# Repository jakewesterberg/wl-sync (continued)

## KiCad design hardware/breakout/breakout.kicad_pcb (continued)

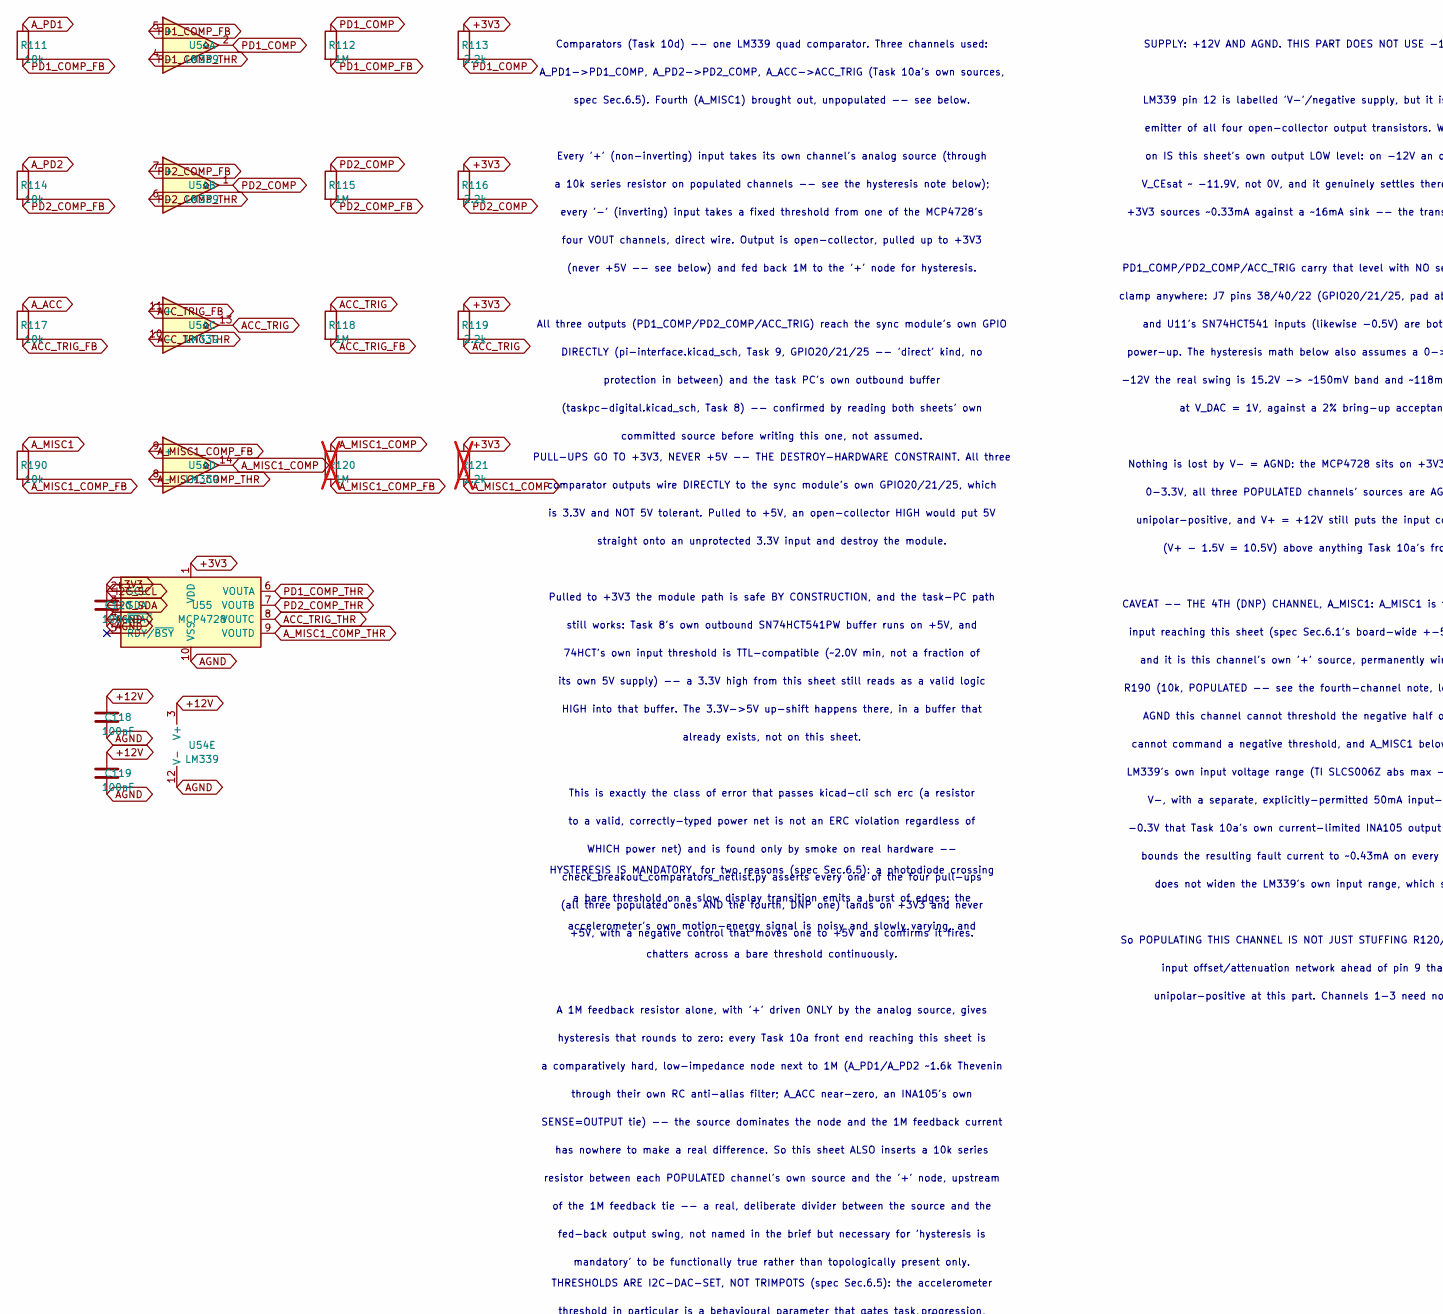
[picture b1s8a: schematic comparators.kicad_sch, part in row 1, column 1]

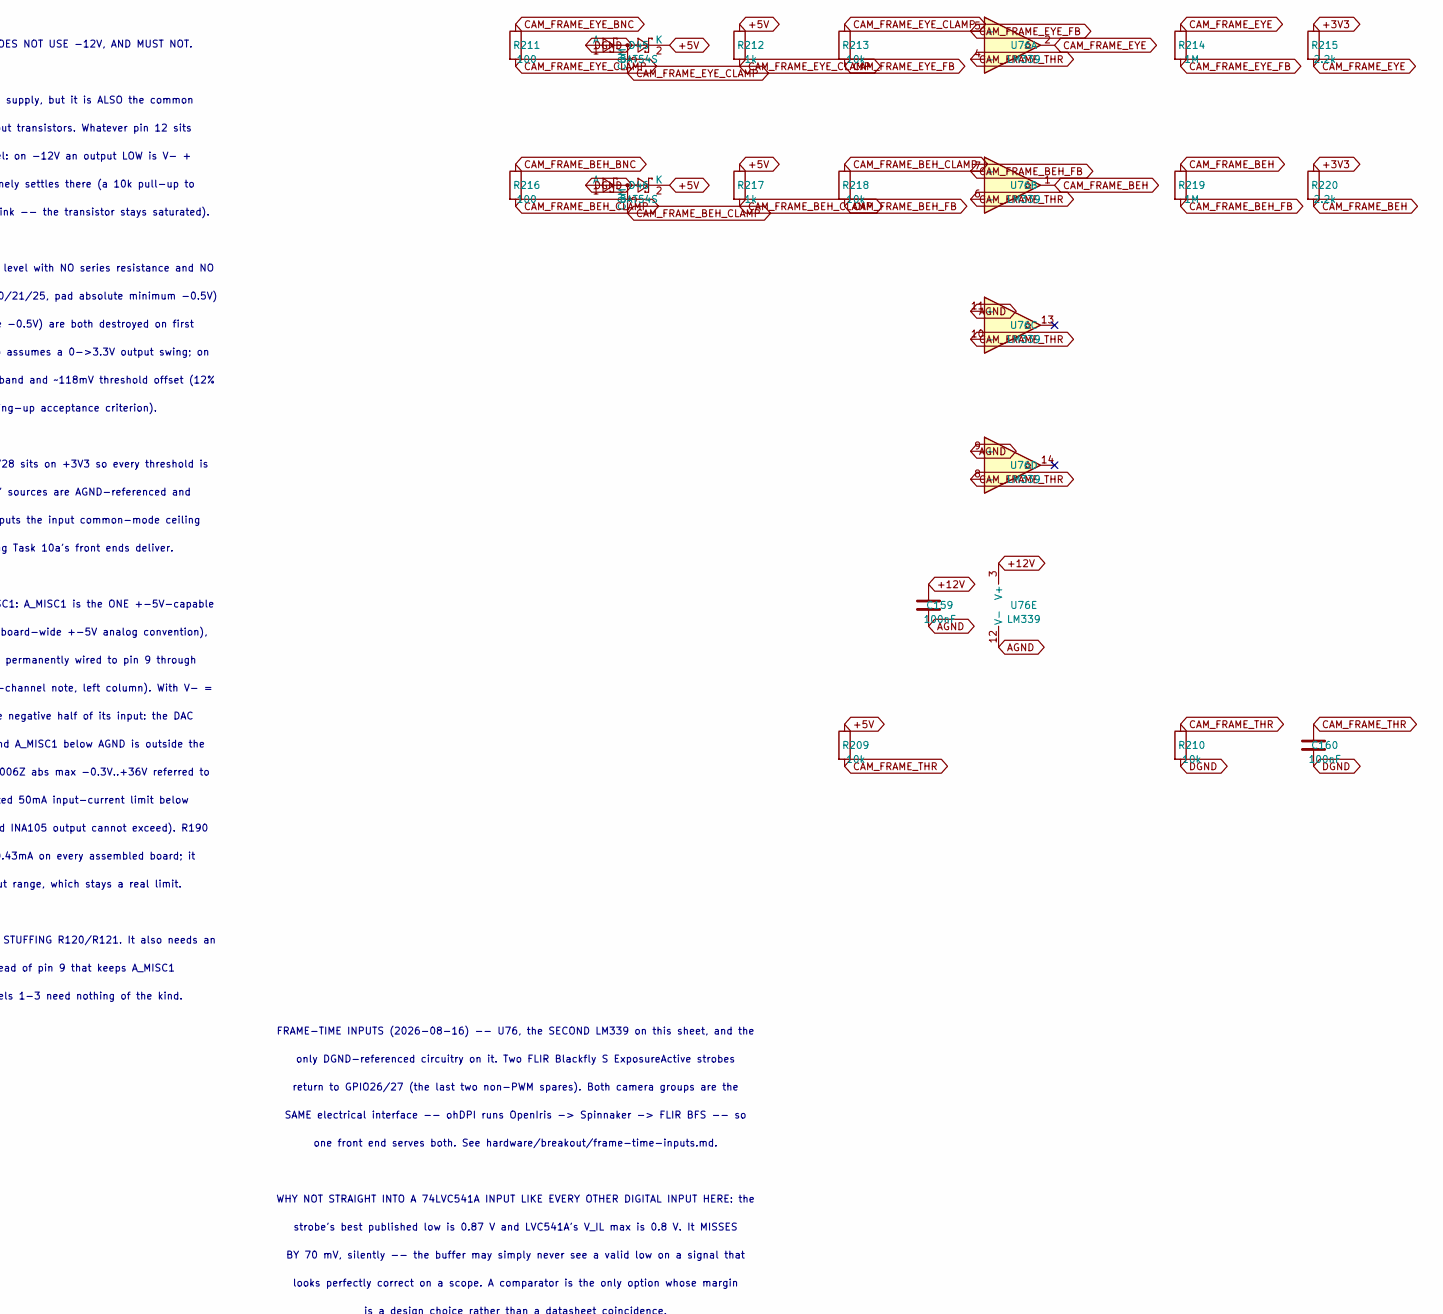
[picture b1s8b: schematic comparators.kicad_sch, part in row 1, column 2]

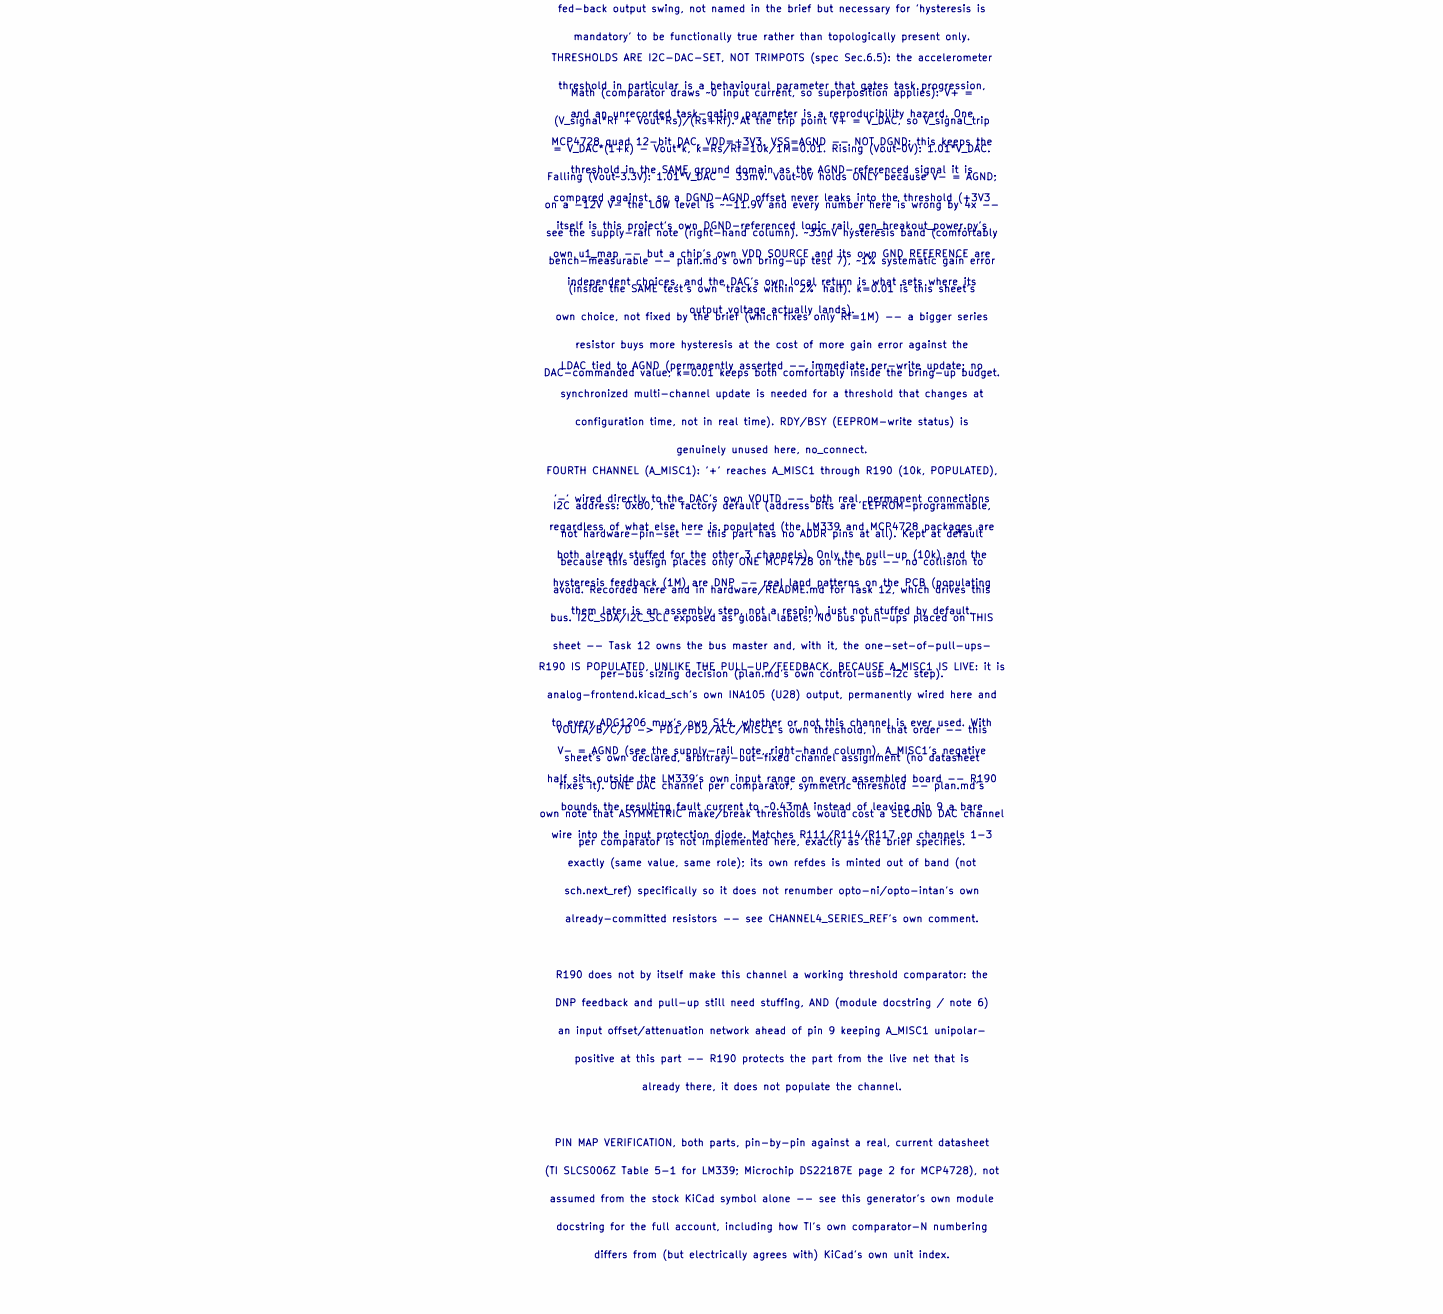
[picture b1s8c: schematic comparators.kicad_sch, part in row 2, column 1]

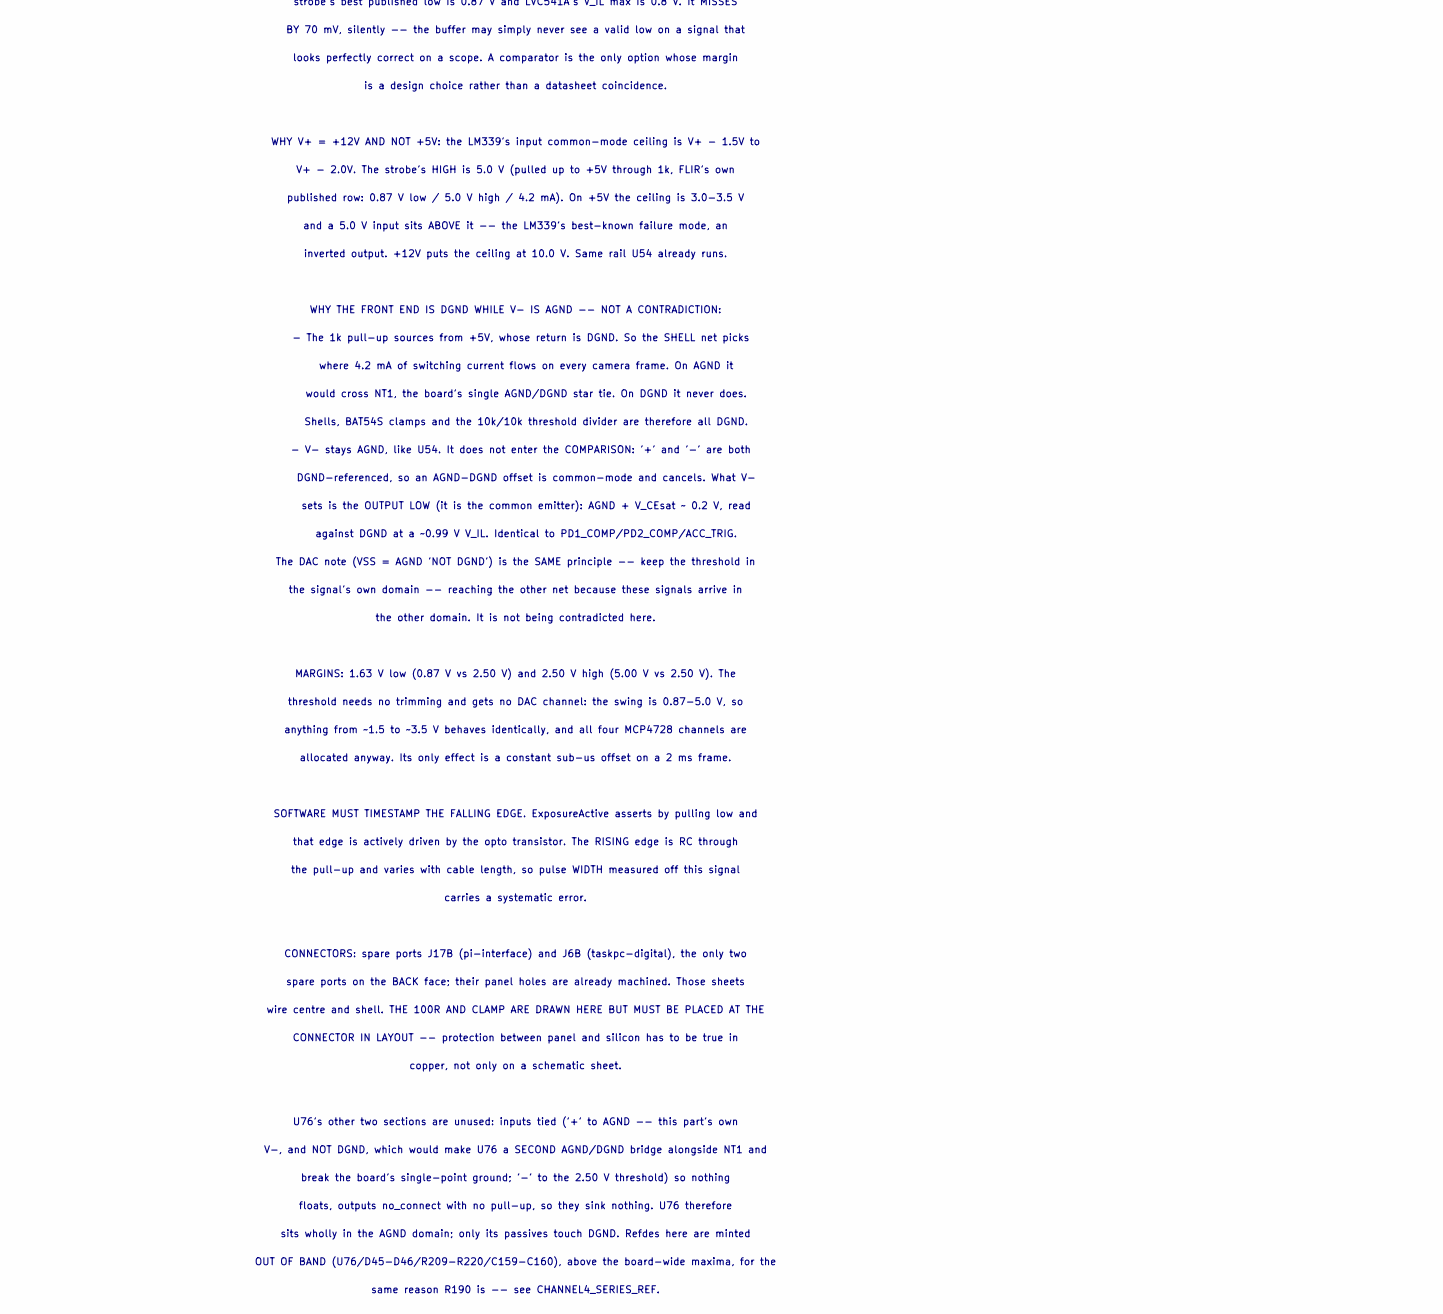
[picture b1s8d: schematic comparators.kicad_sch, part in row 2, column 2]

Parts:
C118, C119, C120, C159, C160: 100nF; C_0603_1608Metric
D45, D46: BAT54S; SOT-23
R111, R114, R117, R190, R209, R210, R213, R218: 10k; R_0603_1608Metric
R112, R115, R118, R214, R219: 1M; R_0603_1608Metric
R113, R116, R119, R215, R220: 2.2k; R_0603_1608Metric
R120: 1M; R_0603_1608Metric; not fitted
R121: 2.2k; R_0603_1608Metric; not fitted
R211, R216: 100; R_0603_1608Metric
R212, R217: 1k; R_0603_1608Metric
U54, U76: LM339; SOIC-14_3.9x8.7mm_P1.27mm
U55: MCP4728; MSOP-10_3x3mm_P0.5mm

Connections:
+3V3: C120.1, R113.1, R116.1, R119.1, R121.1, R215.1, R220.1, U55.1 (VDD); also elsewhere on the board
ACC_TRIG: R118.1, R119.2, U54.13; also elsewhere on the board
ACC_TRIG_FB: R117.2, R118.2, U54.11 (+)
ACC_TRIG_THR: U54.10 (-), U55.8 (VOUTC)
A_ACC: R117.1; also elsewhere on the board
A_MISC1: R190.1; also elsewhere on the board
A_MISC1_COMP: R120.1, R121.2, U54.14
A_MISC1_COMP_FB: R120.2, R190.2, U54.9 (+)
A_MISC1_COMP_THR: U54.8 (-), U55.9 (VOUTD)
A_PD1: R111.1; also elsewhere on the board
A_PD2: R114.1; also elsewhere on the board
CAM_FRAME_BEH: R219.1, R220.2, U76.1; also elsewhere on the board
CAM_FRAME_BEH_BNC: R216.1; also elsewhere on the board
CAM_FRAME_BEH_CLAMP: D46.3 (COM), R216.2, R217.2, R218.1
CAM_FRAME_BEH_FB: R218.2, R219.2, U76.7 (+)
CAM_FRAME_EYE: R214.1, R215.2, U76.2; also elsewhere on the board
CAM_FRAME_EYE_BNC: R211.1; also elsewhere on the board
CAM_FRAME_EYE_CLAMP: D45.3 (COM), R211.2, R212.2, R213.1
CAM_FRAME_EYE_FB: R213.2, R214.2, U76.5 (+)
CAM_FRAME_THR: C160.1, R209.2, R210.1, U76.4 (-), U76.6 (-), U76.8 (-), U76.10 (-)
I2C_SCL: U55.2 (SCL); also elsewhere on the board
I2C_SDA: U55.3 (SDA); also elsewhere on the board
PD1_COMP: R112.1, R113.2, U54.2; also elsewhere on the board
PD1_COMP_FB: R111.2, R112.2, U54.5 (+)
PD1_COMP_THR: U54.4 (-), U55.6 (VOUTA)
PD2_COMP: R115.1, R116.2, U54.1; also elsewhere on the board
PD2_COMP_FB: R114.2, R115.2, U54.7 (+)
PD2_COMP_THR: U54.6 (-), U55.7 (VOUTB)

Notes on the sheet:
Comparators (Task 10d) -- one LM339 quad comparator. Three channels used:
A_PD1->PD1_COMP, A_PD2->PD2_COMP, A_ACC->ACC_TRIG (Task 10a's own sources,
spec Sec.6.5). Fourth (A_MISC1) brought out, unpopulated -- see below.
Every '+' (non-inverting) input takes its own channel's analog source (through
a 10k series resistor on populated channels -- see the hysteresis note below);
every '-' (inverting) input takes a fixed threshold from one of the MCP4728's
four VOUT channels, direct wire. Output is open-collector, pulled up to +3V3
(never +5V -- see below) and fed back 1M to the '+' node for hysteresis.
All three outputs (PD1_COMP/PD2_COMP/ACC_TRIG) reach the sync module's own GPIO
DIRECTLY (pi-interface.kicad_sch, Task 9, GPIO20/21/25 -- 'direct' kind, no
protection in between) and the task PC's own outbound buffer
(taskpc-digital.kicad_sch, Task 8) -- confirmed by reading both sheets' own
committed source before writing this one, not assumed.
PULL-UPS GO TO +3V3, NEVER +5V -- THE DESTROY-HARDWARE CONSTRAINT. All three
comparator outputs wire DIRECTLY to the sync module's own GPIO20/21/25, which
is 3.3V and NOT 5V tolerant. Pulled to +5V, an open-collector HIGH would put 5V
straight onto an unprotected 3.3V input and destroy the module.
Pulled to +3V3 the module path is safe BY CONSTRUCTION, and the task-PC path
still works: Task 8's own outbound SN74HCT541PW buffer runs on +5V, and
74HCT's own input threshold is TTL-compatible (~2.0V min, not a fraction of
its own 5V supply) -- a 3.3V high from this sheet still reads as a valid logic
HIGH into that buffer. The 3.3V->5V up-shift happens there, in a buffer that
already exists, not on this sheet.
This is exactly the class of error that passes kicad-cli sch erc (a resistor
to a valid, correctly-typed power net is not an ERC violation regardless of
WHICH power net) and is found only by smoke on real hardware --
check_breakout_comparators_netlist.py asserts every one of the four pull-ups
(all three populated ones AND the fourth, DNP one) lands on +3V3 and never
+5V, with a negative control that moves one to +5V and confirms it fires.
HYSTERESIS IS MANDATORY, for two reasons (spec Sec.6.5): a photodiode crossing
a bare threshold on a slow display transition emits a burst of edges; the
accelerometer's own motion-energy signal is noisy and slowly varying, and
chatters across a bare threshold continuously.
A 1M feedback resistor alone, with '+' driven ONLY by the analog source, gives
hysteresis that rounds to zero: every Task 10a front end reaching this sheet is
a comparatively hard, low-impedance node next to 1M (A_PD1/A_PD2 ~1.6k Thevenin
through their own RC anti-alias filter; A_ACC near-zero, an INA105's own
SENSE=OUTPUT tie) -- the source dominates the node and the 1M feedback current
has nowhere to make a real difference. So this sheet ALSO inserts a 10k series
resistor between each POPULATED channel's own source and the '+' node, upstream

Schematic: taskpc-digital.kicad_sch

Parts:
C22, C23, C24, C25, C26, C27, C28, C30, C31, C150, C151, C152, C153, C154: 100nF; C_0603_1608Metric
C29, C149: 1uF; C_0603_1608Metric
D4, D5, D6, D7, D8, D9, D10, D11, D12, D13, D14, D15, D16, D17, D18, D19, D20, D21, D22: BAT54S; SOT-23
J2: Connector 0 (analog + AISENSE, task PC NI); MDR68_Male_RightAngle
J3: Connector 1 (digital, task PC NI); MDR68_Male_RightAngle
J4: Manual reward button (panel, recessed); SW_PUSH-12mm
J5: Dual panel BNC: Remote reward BNC (parallel to pa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; BNC_Dual_RA_Isolated
J6: Dual panel BNC: Reward driver out (BNC) | Behavio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; BNC_Dual_RA_Isolated
J57: Dual panel BNC: Line-out L (task PC AO 0) | Line-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; BNC_Dual_RA_Isolated
R5, R6, R7, R8, R9, R10, R11, R12, R13, R14, R15, R16, R17, R18, R19, R20, R21, R22, R23, R203, R221, R222, R223: 100; R_0603_1608Metric
R24: 10k; R_0603_1608Metric
R191: 442k; R_0603_1608Metric
U5, U6, U7: SN74LVC541APW; Texas_PW0020A_TSSOP-20_4.4x6.5mm_P0.65mm
U8, U9, U10, U11, U70, U71, U72, U73: SN74AHCT541PW; Texas_PW0020A_TSSOP-20_4.4x6.5mm_P0.65mm
U12: SN74HCT32D; SOIC-14_3.9x8.7mm_P1.27mm
U13: SN74HCT14D; SOIC-14_3.9x8.7mm_P1.27mm
U69: 74HCT123D; SOIC-16_3.9x9.9mm_P1.27mm

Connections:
+3V3: C22.1, C23.1, C24.1, U5.20 (VCC), U6.20 (VCC), U7.20 (VCC); also elsewhere on the board
ACC_TRIG: U11.4 (A2); also elsewhere on the board
ACC_TRIG_TPC: J3.40, U11.16 (Y2)
AO_GND_TPC: J2.54, J2.55, J57.2 (A_Ext), J57.4 (B_Ext)
AO_L_BNC: J57.1 (A_In), R221.2
AO_L_TPC: J2.22, R221.1
AO_R_BNC: J57.3 (B_In), R222.2
AO_R_TPC: J2.21, R222.1
A_EYE_LX_TPC: J2.68; also elsewhere on the board
A_EYE_LY_TPC: J2.33; also elsewhere on the board
A_EYE_RX_TPC: J2.65; also elsewhere on the board
A_EYE_RY_TPC: J2.30; also elsewhere on the board
A_JOY_X_TPC: J2.28; also elsewhere on the board
A_JOY_Y_TPC: J2.60; also elsewhere on the board
A_MISC1_TPC: J2.25; also elsewhere on the board
A_MISC2_TPC: J2.57; also elsewhere on the board
A_MISC3_TPC: J2.34; also elsewhere on the board
CAM_FRAME_BEH_BNC: J6.3 (B_In); also elsewhere on the board
EVT_D0_BUF: U8.18 (Y0), U70.18 (Y0); also elsewhere on the board
EVT_D0_CLAMP: D4.3 (COM), R5.2, U5.2 (A0), U8.2 (A0), U70.2 (A0)
EVT_D0_PI: U5.18 (Y0); also elsewhere on the board
EVT_D0_TPC: J3.52, R5.1
EVT_D1_BUF: U8.17 (Y1), U70.17 (Y1); also elsewhere on the board
EVT_D1_CLAMP: D5.3 (COM), R6.2, U5.3 (A1), U8.3 (A1), U70.3 (A1)
EVT_D1_PI: U5.17 (Y1); also elsewhere on the board
EVT_D1_TPC: J3.17, R6.1
EVT_D2_BUF: U8.16 (Y2), U70.16 (Y2); also elsewhere on the board
EVT_D2_CLAMP: D6.3 (COM), R7.2, U5.4 (A2), U8.4 (A2), U70.4 (A2)
EVT_D2_PI: U5.16 (Y2); also elsewhere on the board
EVT_D2_TPC: J3.49, R7.1
EVT_D3_BUF: U8.15 (Y3), U70.15 (Y3); also elsewhere on the board
EVT_D3_CLAMP: D7.3 (COM), R8.2, U5.5 (A3), U8.5 (A3), U70.5 (A3)
EVT_D3_PI: U5.15 (Y3); also elsewhere on the board
EVT_D3_TPC: J3.47, R8.1
EVT_D4_BUF: U8.14 (Y4), U70.14 (Y4); also elsewhere on the board
EVT_D4_CLAMP: D8.3 (COM), R9.2, U5.6 (A4), U8.6 (A4), U70.6 (A4)
EVT_D4_PI: U5.14 (Y4); also elsewhere on the board
EVT_D4_TPC: J3.19, R9.1
EVT_D5_BUF: U8.13 (Y5), U70.13 (Y5); also elsewhere on the board
EVT_D5_CLAMP: D9.3 (COM), R10.2, U5.7 (A5), U8.7 (A5), U70.7 (A5)
EVT_D5_PI: U5.13 (Y5); also elsewhere on the board
EVT_D5_TPC: J3.51, R10.1
EVT_D6_BUF: U8.12 (Y6), U70.12 (Y6); also elsewhere on the board
EVT_D6_CLAMP: D10.3 (COM), R11.2, U5.8 (A6), U8.8 (A6), U70.8 (A6)
EVT_D6_PI: U5.12 (Y6); also elsewhere on the board
EVT_D6_TPC: J3.16, R11.1
EVT_D7_BUF: U8.11 (Y7), U70.11 (Y7); also elsewhere on the board
EVT_D7_CLAMP: D11.3 (COM), R12.2, U5.9 (A7), U8.9 (A7), U70.9 (A7)
EVT_D7_PI: U5.11 (Y7); also elsewhere on the board
EVT_D7_TPC: J3.48, R12.1
EVT_D8_BUF: U9.18 (Y0), U71.18 (Y0); also elsewhere on the board
EVT_D8_CLAMP: D12.3 (COM), R13.2, U6.2 (A0), U9.2 (A0), U71.2 (A0)
EVT_D8_PI: U6.18 (Y0); also elsewhere on the board
EVT_D8_TPC: J3.11, R13.1
EVT_D9_BUF: U9.17 (Y1), U71.17 (Y1); also elsewhere on the board
EVT_D9_CLAMP: D13.3 (COM), R14.2, U6.3 (A1), U9.3 (A1), U71.3 (A1)
EVT_D9_PI: U6.17 (Y1); also elsewhere on the board
EVT_D9_TPC: J3.10, R14.1
EVT_D10_BUF: U9.16 (Y2), U71.16 (Y2); also elsewhere on the board
EVT_D10_CLAMP: D14.3 (COM), R15.2, U6.4 (A2), U9.4 (A2), U71.4 (A2)
EVT_D10_PI: U6.16 (Y2); also elsewhere on the board
EVT_D10_TPC: J3.43, R15.1
EVT_D11_BUF: U9.15 (Y3), U71.15 (Y3); also elsewhere on the board
EVT_D11_CLAMP: D15.3 (COM), R16.2, U6.5 (A3), U9.5 (A3), U71.5 (A3)
EVT_D11_PI: U6.15 (Y3); also elsewhere on the board
EVT_D11_TPC: J3.42, R16.1
EVT_D12_BUF: U9.14 (Y4), U71.14 (Y4); also elsewhere on the board
EVT_D12_CLAMP: D16.3 (COM), R17.2, U6.6 (A4), U9.6 (A4), U71.6 (A4)
EVT_D12_PI: U6.14 (Y4); also elsewhere on the board
EVT_D12_TPC: J3.41, R17.1
EVT_D13_BUF: U9.13 (Y5), U71.13 (Y5); also elsewhere on the board
EVT_D13_CLAMP: D17.3 (COM), R18.2, U6.7 (A5), U9.7 (A5), U71.7 (A5)
EVT_D13_PI: U6.13 (Y5); also elsewhere on the board
EVT_D13_TPC: J3.6, R18.1
EVT_D14_BUF: U9.12 (Y6), U71.12 (Y6); also elsewhere on the board
EVT_D14_CLAMP: D18.3 (COM), R19.2, U6.8 (A6), U9.8 (A6), U71.8 (A6)
EVT_D14_PI: U6.12 (Y6); also elsewhere on the board
EVT_D14_TPC: J3.5, R19.1
EVT_D15_BUF: U9.11 (Y7), U71.11 (Y7); also elsewhere on the board
EVT_D15_CLAMP: D19.3 (COM), R20.2, U6.9 (A7), U9.9 (A7), U71.9 (A7)
EVT_D15_PI: U6.11 (Y7); also elsewhere on the board
EVT_D15_TPC: J3.38, R20.1
EVT_STROBE_BUF: U10.18 (Y0), U72.18 (Y0); also elsewhere on the board
EVT_STROBE_CLAMP: D20.3 (COM), R21.2, U7.2 (A0), U10.2 (A0), U10.5 (A3), U72.2 (A0), U72.5 (A3)
EVT_STROBE_INTAN_BUF: U10.15 (Y3), U72.15 (Y3); also elsewhere on the board
EVT_STROBE_PI: U7.18 (Y0); also elsewhere on the board
EVT_STROBE_TPC: J3.37, R21.1
PD1_COMP: U11.2 (A0), U11.6 (A4), U73.2 (A0); also elsewhere on the board
PD1_COMP_BUF: U11.14 (Y4), U73.18 (Y0); also elsewhere on the board
PD1_COMP_PFI: J2.38, R223.2
PD1_COMP_PFI_BUF: R223.1; also elsewhere on the board
PD1_COMP_TPC: J3.46, U11.18 (Y0)
PD2_COMP: U11.3 (A1), U11.7 (A5), U73.3 (A1); also elsewhere on the board
PD2_COMP_BUF: U11.13 (Y5), U73.17 (Y1); also elsewhere on the board
PD2_COMP_TPC: J3.2, U11.17 (Y1)
RHS_STIM_OUT: U11.5 (A3), U11.8 (A6), U11.9 (A7); also elsewhere on the board
RHS_STIM_OUT_BUF: U11.11 (Y7), U11.12 (Y6); also elsewhere on the board
RHS_STIM_OUT_TPC: J3.1, U11.15 (Y3)
RWD_BTN: C29.1, J4.1, J5.1 (A_In), R24.2, U13.1
RWD_BTN_DEB: U13.2, U69.2 (B)
RWD_BTN_PULSE: U12.2, U69.13 (Q)
RWD_CMD: U7.17 (Y1), U12.1; also elsewhere on the board
RWD_CMD_BUF: U10.17 (Y1), U72.17 (Y1); also elsewhere on the board
RWD_CMD_CLAMP: D21.3 (COM), R22.2, U7.3 (A1), U10.3 (A1), U10.6 (A4), U72.3 (A1), U72.6 (A4)
RWD_CMD_INTAN_BUF: U10.14 (Y4), U72.14 (Y4); also elsewhere on the board
RWD_CMD_TPC: J3.3, R22.1
RWD_DLVR: R203.1, U10.8 (A6), U10.9 (A7), U12.3, U72.8 (A6), U72.9 (A7); also elsewhere on the board
RWD_DLVR_BNC: J6.1 (A_In), R203.2
RWD_DLVR_BUF: U10.12 (Y6), U72.12 (Y6); also elsewhere on the board
RWD_DLVR_INTAN_BUF: U10.11 (Y7), U72.11 (Y7); also elsewhere on the board
STIM_TRIG: U7.16 (Y2); also elsewhere on the board
STIM_TRIG_BUF: U10.16 (Y2), U72.16 (Y2); also elsewhere on the board
STIM_TRIG_CLAMP: D22.3 (COM), R23.2, U7.4 (A2), U10.4 (A2), U10.7 (A5), U72.4 (A2), U72.7 (A5)
STIM_TRIG_INTAN_BUF: U10.13 (Y5), U72.13 (Y5); also elsewhere on the board
STIM_TRIG_TPC: J3.45, R23.1
U69_CEXT: C149.2, U69.14 (Cext)
U69_RCEXT: C149.1, R191.2, U69.15 (RCext)

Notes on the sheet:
All 23 task-PC digital lines (19 out + 4 in) ride Connector 1, P0.8-P0.30 of
pinout and TSSOP-20 footprint, both symbols extend the same 74LS541 KiCad
place_reward_oneshot()'s own docstring for the full account. Real part:
It also fixes a PACKAGE limit no per-pin check can see. AHCT541's GND-pin
return. PD1_COMP_PFI_BUF comes from pi-interface's SN74LVC541A channel 1 (3.3 V
minimum, because the +5V rail reaches them through F4 and D3 and the original
the sync module recording reward-delivered continuously. Same failure
actual polarity against MonkeyLogic before commissioning (MonkeyLogic's own
taps -- the established fan-out point, one protection network with N buffered
AISENSE=pin62 -> AGND (NRSE reference -- spec Decision 5; the easiest wire on
in series sharing one node, per TI SLVA720A Fig.3-1's own topology, NOT each
These four packages carry the SECOND output of every LED pair. They exist
CMOS inputs and a panel header: ~0mA DC out of the 74HCT32.
LEDs were never guaranteed to switch (~5mA worst case against a 7.0mA I_FH
P0.30=pin1(RHS_STIM_OUT) P0.31=pin39 (spare, no_connect). D GND (all 12 real
AI0=pin68=A_EYE_LX_TPC AI1=pin33=A_EYE_LY_TPC AI2=pin65=A_EYE_RX_TPC
out against the card's 2.2 V V_IH); PFI 7, not PFI 12-15, the default counter
AI3=pin30=A_EYE_RY_TPC AI4=pin28=A_JOY_X_TPC AI5=pin60=A_JOY_Y_TPC
signature as the reward-OR polarity defect caught here at fix round 1.
U69/R191/C149-C150 already use here. An ordinary next_ref() would renumber
CHANNELS 4/5 (PD1_COMP_BUF, PD2_COMP_BUF) ARE NOT OUTBOUND -- they do not reach
separate 58.6mA-of-70mA concern on U8/U9/U10 too.
clamp circuitry lives on THIS sheet, only the labelled connection point does.
Reward OR polarity (fix round 1, finding 1 -- CRITICAL): RWD_BTN idles HIGH
RewardPolarity setting must be HIGH to match this board -- hardware/README.md):
which one AHCT541 output cannot sink. Neither value is shippable alone.
own front-end/buffer outputs (plan.md Task 10 Step 3) -- no buffer/series-R/
ch5 STIM_TRIG_CLAMP -> STIM_TRIG_INTAN_BUF (opto-intan U65 ch1)
U69 (Nexperia 74HCT123D) gives every hand-delivered reward a FIXED ~199ms
Connector 0/Connector 1 split confirmed from NI's own device specifications
buffered leg instead of hanging directly on PD1_COMP/PD2_COMP, which wire
cannot extend the pulse; retriggering only matters for a second physical
DRIVER PART IS SN74AHCT541PW, NOT SN74HCT541PW (Value/MPN only -- identical
TWO BUFFER OUTPUTS PER OPTOCOUPLER LED (finding F1b, 2026-08-16).
Table 4 row 1) -- genuinely inert, not merely untriggered. Pin map verified
(6 spare channels, the headroom finding F4's camera triggers need)
and injecting ~7mA into an unpowered pad whenever this board is on and the sync
sizing used a nominal 5.00V and a TYPICAL V_F) -- and 249R draws ~12.7mA,
threshold, not a driver choice. HCT541's own rated IOL is 6mA (7.33mA is 22%
around: a single continuous hold produces exactly one rising edge on the

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
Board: 4 copper layers, 577 parts (0 on the bottom side), 447 nets, no tracks yet.

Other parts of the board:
H1, H2: M2.5 standoff, CM5 IO Board; MountingHole_2.7mm_M2.5
H3, H4, H5, H6, H7, H8, H9, H10: M3 mounting hole, unplated (M-16); MountingHole_3.2mm_M3
R224: 0R/10R; R_0603_1608Metric

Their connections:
ACCESIO_SHELL: R224.1; also elsewhere on the board

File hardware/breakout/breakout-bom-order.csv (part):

"Reference","Value","Footprint","Order Code","Note"
"C1,C3,C5,C8,C10,C11,C14,C16,C17,C20,C133,C135,C136,C138,C147,C155","10uF","Capacitor_SMD:C_0805_2012Metric,Capacitor_SMD:C_1206_3216Metric","GENERIC — not a locked MPN","0805 (power.kicad_sch) or 1206 (opto sheets) X7R ceramic; 5+ mfr (Yageo/Murata/Kemet/Samsung/TDK/Vishay/Panasonic) — procurement-check.md §5.4/§7. Row includes 2 DNP refs (C135, C136) — §2. C147 is power.kicad_sch's own FAN_12V bulk cap (fan-header addendum), same 0805/X7R class, no new sourcing question."
"C2,C4,C6,C7,C9,C15,C21-C28,C30-C47,C52,C53,C58-C132,C134,C137,C139-C143,C145,C146,C148,C150-C154,C156-C158,C159,C160","100nF","Capacitor_SMD:C_0603_1608Metric","GENERIC — not a locked MPN","0603 X7R ceramic, multi-source — §5.4. C148 is power.kicad_sch's own FAN_12V small-signal decoupling cap (fan-header addendum); C150 is the panel-instrumentation task's own reward one-shot (U69) decoupling cap (2026-08-15) — same 0603/X7R class as every other IC decoupler on this board, no new sourcing question. C29 LEAVES this group (panel-instrumentation task) — it is the reward debounce cap, now 1uF, not 100nF — see that row below. Frame-time inputs (2026-08-16, comparators.kicad_sch U76) fold in here: same value, footprint and commodity sourcing as the rest of this row, no new sourcing question."
"C12,C13,C18,C19","10nF","Capacitor_SMD:C_0603_1608Metric","GENERIC — not a locked MPN","0603 ceramic, multi-source — §5.4."
"C29,C149","1uF","Capacitor_SMD:C_0603_1608Metric","GENERIC — not a locked MPN","0603 X7R ceramic (16V-rated 1uF in 0603 is a common, real, multi-source value), multi-source — §5.4. Panel-instrumentation task (2026-08-15): C29 is the reward debounce cap (10k x 1uF = 10ms, spec Sec.3.1, up from 100nF — see the 100nF row's own note for why it moved out of that group), C149 is the reward one-shot's own Cext timing capacitor (gen_breakout_taskpc_digital.py's own place_reward_oneshot() docstring)."
"C48,C50","22pF","Capacitor_SMD:C_0603_1608Metric","GENERIC — not a locked MPN","0603 C0G/NP0 ceramic — C0G is required here, not X7R: this is a TIA compensation capacitor and its value must not shift with bias or temperature. NEW value at finding M1 (2026-08-16), was 3.3pF."
"C49,C51","6.8nF","Capacitor_SMD:C_0603_1608Metric","GENERIC — not a locked MPN","0603 ceramic, multi-source — §5.4."
"C54","1.2nF","Capacitor_SMD:C_0603_1608Metric","GENERIC — not a locked MPN","0603 ceramic, multi-source — §5.4."
"C55","1.0nF","Capacitor_SMD:C_0603_1608Metric","GENERIC — not a locked MPN","0603 ceramic, multi-source — §5.4."
"C56","1.5nF","Capacitor_SMD:C_0603_1608Metric","GENERIC — not a locked MPN","0603 ceramic, multi-source — §5.4."
"C57","220pF","Capacitor_SMD:C_0603_1608Metric","GENERIC — not a locked MPN","0603 ceramic, multi-source — §5.4."
"C144","220nF","Capacitor_SMD:C_0603_1608Metric","GENERIC — not a locked MPN","0603 ceramic, multi-source — §5.4."
"C161","4.7uF/50V","Capacitor_SMD:C_1210_3225Metric","C3225X7R1H475K250AB","TDK. NEW at layout task L1 (2026-11-20): C1 of U63's EN 55032 class A input filter, across +5V/DGND on the source side of L1. Value, rating, dielectric and package are Traco's: '4.7 uF / 50 V, 1210 X7R' -- Traco 'TMR 1(SM) Series -- EMI Consideration' rev. 2021-12-15 p.1, table row TMR 1-05xx (hardware/datasheet-params.toml [tmr_1_0511] emc_filter_*). 4.7 uF +/-10%, 50 V, X7R, 1210. A LOCKED MPN, unlike this board's other ceramics: the 50 V rating on a 5 V rail is Traco's and is what keeps the capacitance under DC bias, so do not substitute a lower-voltage 4.7 uF. LIFECYCLE STATUS CONTESTED -- CONFIRM AT ORDER: DigiKey (product 2733161; 12-wk mfr lead) and Future listed it Active on 2026-11-20, while the L1 review the same day reports RS Components listing it discontinued; all search-result-level evidence, none of it TDK's own word. SECOND SOURCE, same rating in every term (4.7 uF +/-10%, 50 V, X7R, 1210): KEMET C1210C475K5RACTU (DigiKey product 3095476, listed Active 2026-11-20) -- not C1210X475K5RACTU, a different series. Murata GRM32ER71H475KA88L is the same spec but was shown NRND by two sources the same day; not chosen for that reason."
"C162","220pF/2kV","Capacitor_SMD:C_1808_4520Metric","C1808C221KGRACTU","KEMET. NEW at layout task L1 (2026-11-20): C2 of U63's EN 55032 class A input filter. Value, rating, dielectric and package are Traco's: '220 pF / 2 kV, 1808 X7R' -- Traco 'TMR 1(SM) Series -- EMI Consideration' rev. 2021-12-15 p.1, table row TMR 1-05xx (hardware/datasheet-params.toml [tmr_1_0511] emc_filter_*). 220 pF +/-10%, 2000 V, X7R, 1808. A LOCKED MPN AND A LOCKED RATING: this capacitor CROSSES THE ISOLATION BARRIER (U63 -Vin to -Vout, DGND to ISO_5V_RTN), so the 2 kV rating against the converter's 1500 VDC isolation is the whole point -- an ordinary 50 V 220 pF here defeats the barrier. Do not confuse with C1808C221KHRACTU (3 kV) or C1808C222KGRACTU (2.2 nF). Listed at DigiKey (product 2235394; 12-wk mfr lead) on 2026-11-20, search-result-level evidence -- confirm stock at order time. FITTED on every board; whether it stays is a bring-up measurement (parametric-audit.md ruling R4, hardware/assembly-checklist.md): with it the DGND-to-Intan-reference coupling is about 330 pF, without it about 110 pF."
"D1-D3,D44","SS14","Diode_SMD:D_SMA_Handsoldering","GENERIC — not a locked MPN","Commodity Schottky, multi-mfr (onsemi/MCC/Diotec/Nexperia/SMC/TSC) — §5.3."
"D4-D39,D45,D46","BAT54S","Package_TO_SOT_SMD:SOT-23","GENERIC — not a locked MPN","Commodity dual-diode, same multi-mfr list — §5.3. Frame-time inputs (2026-08-16, comparators.kicad_sch U76) fold in here: same value, footprint and commodity sourcing as the rest of this row, no new sourcing question."
"D40-D43","LED","LED_SMD:LED_0603_1608Metric_Pad1.05x0.95mm_HandSolder","GENERIC — not a locked MPN","0603 SMD indicator LED, multi-source (any 0603 red/green ~2V Vf part; Kingbright/Lite-On/Rohm/Everlight all stock equivalents) — commodity, no supply risk. Panel-instrumentation task (2026-08-15, spec Sec.9.8): D40/D41/D42 are the +12V/-12V/+5V power-good indicators (R192/R193/R194 their own series resistors, ~4.5mA target); D43 is the barcode heartbeat LED (R195, ~7.7mA target) — see gen_breakout_power.py's own _place_power_good_leds() and gen_breakout_pi_interface.py's own trigger-buffer section for the derivations. Exact color/part is a layout-stage/procurement decision, same status as every BNC's own MPN on this board."
"F1-F3","1206L050/15YR","Fuse:Fuse_1206_3216Metric_Pad1.42x1.75mm_HandSolder","1206L050/15YR","Littelfuse. Active, PPTC resettable fuse (500mA hold / 1A trip / 15V max), 1206. 122,476 in stock at DigiKey, 13-week mfr lead — well-stocked at this 8-unit run size (grew from 5 -- panel-instrumentation task, 2026-08-15, spec Sec.9.8: F2/F3/F4 are the +12V/-12V/+5V main-input fuses, same real part as F1's own fan feed, reused rather than a fourth new fuse number — see gen_breakout_power.py's own _place_inlet() docstring for the sizing rationale and the +-12V margin caveat, flagged there for bench confirmation) — procurement-check.md addendum."
"F4","1206L110-C","Fuse:Fuse_1206_3216Metric_Pad1.42x1.75mm_HandSolder","1206L110-C","Littelfuse. PPTC resettable fuse (1.10A hold / 2.20A trip / 6V max), 1206. NEW at finding M7 (2026-08-16) — F4 alone, NOT the same part as F1/F2/F3. The +5V rail carries 392mA typ / 495mA max once finding F1 raised the optocoupler drive, and 1206L050 holds only ~0.44A at this chassis's 35°C ambient, so it would trip in normal operation. NOTE V_max is 6Vdc, not 15 — in the 1206L series the elevated-voltage variants exist only at the two lowest hold currents, so this part suits +5V and MUST NOT be substituted onto the ±12V rails. Confirm stock and current revision before ordering; figures here are read from the 2006 Electronics Designers Guide revision (Littelfuse's own asset URL returns 403)."
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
